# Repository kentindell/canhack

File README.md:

## Welcome to the Yes We CAN repository

This repository contains tools and resources for the <b>Yes We CAN</b> project of [Canis Labs](https://canislabs.com). There are several related projects here:

- Support for the [Canis Labs](https://canislabs.com) [CANPico](https://canislabs.com/canpico) (an add-on CAN hardware board for the Raspberry Pi Pico)
- CANHack toolkit (a proof-of-concept low-level CAN protocol hacking library)
- Sigrok CAN protocol decoder (allowing PulseView to decode CAN frames and indicate exceptional low-level protocol events)
- A Python tool for creating CAN frame bit sequences

Canis Labs CTO Dr. Ken Tindell writes about CAN on his blog at: https://kentindell.github.io

## CAN FD extension

This adds experimental **CAN FD** support to the CANHack toolkit (bit-banged, fixed
500 kbit/s arbitration / 2 Mbit/s data), from the bachelor thesis of Fynn Denecke.

- Build it from the repository root with **`./build.sh`** — see **[BUILDING.md](BUILDING.md)**
  for prerequisites (gcc/cmake/Arm toolchain) and how to point the build at your compiler.
  MicroPython is pinned as a git submodule, so the build fetches its own dependencies.
- Current hardware-verified status, known limits and a scope/PCAN test plan:
  **[CANPico/firmware/CANFD_STATUS.md](CANPico/firmware/CANFD_STATUS.md)**.

## Canis Labs CANPico hardware support

MicroPython firmware and documentation is in the `CANPico` folder. In addition, there is support for
C included in the Canis Labs CAN SDK for C, which has drivers for the MCP25xxFD (the MicroPython firmware
uses this CAN SDK to provide a MicroPython CAN API).

The Canis Labs CAN SDK repository is:

[https://github.com/kentindell/canis-can-sdk](https://github.com/kentindell/canis-can-sdk)

and contains a "hello world" application using the CAN API, with pre-built firmware for the Pico and Pico W
with the CANPico board.

## CANHack toolkit

The CANHack toolkit is a proof-of-concept toolkit of different CAN protocol attacks, showing
the viability of low-level bit-banging attacks on the CAN protocol itself.

It is provided as generic C source code in two files:

    src/
        canhack.c
        canhack.h

It has been built into the Canis Labs MicroPython firmware for the Raspberry Pi Pico and Pico W
for the following hardware:

- Canis Labs [CANPico board](https://canislabs.com/canpico/)
- Canis Labs CANHack board (this uses the same firmware as the CANPico)
- Car Hacking Village DEF CON 30 badge
- Oliver @hartkopp 's [bit-bang-only](docs/BitBangOnlyPico.md) low-cost setup

The MicroPython firmware for the CHV DEF CON 30 badge is located in:

    pico/
        micropython/
            firmware-20220805-CHV-DEFCON30.uf2

Documentation for the MicroPython CANHack API is in:

    CANPico/
        docs/
            CANHack MicroPython SDK reference manual.pdf

The Canis Labs [CTO blog](https://kentindell.github.io) has more information
[on the CANHack toolkit](https://kentindell.github.io/categories#CANHack), including details on how 
to make a CANHack board using breadboard. There is also 
a [CANHack toolkit demo video](https://youtu.be/dATyoWOlEJU) that goes into detail on how to
use the toolkit from Python, the CAN protocol hacks it
includes, and demonstrates it attacking CAN frames in real hardware (NB: the video uses the STM32-based PyBoard,
but the API is the same).

## Sigrok CAN protocol decoder

A [Sigrok](https://sigrok.org) protocol decoder for CAN 2.0:

    src/
        can2/
            __init__.py
            pd.py

There is a [PulseView and can2 demo video](https://youtu.be/RvExJSDvhKo) showing how to use PulseView
as a logic analyzer and seeing CAN frames at a low-level.

The [CIA CAN newsletter](https://https://can-newsletter.org) has published an [article](https://can-newsletter.org/tools/tools-miscellaneous/210607_can-decoder-warns-for-malicious-attacks_cnlm_ken-tindell) describing the protocol decoder and showing how it can spot some CAN protocol attacks.

## Python CAN tool

Python tool for creating and parsing a CAN bitstreams (including creating Janus attack frames):

    src/
        canframe.py

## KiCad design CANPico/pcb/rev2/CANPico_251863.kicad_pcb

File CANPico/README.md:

## CANPico support

This folder contains support files for the Canis Labs CANPico. There are two revisions of the CANPico
but the firmware operates on either version. There is also support for the Raspberry Pi Pico
and the Raspberry Pi Pico W (a Pico with wireless support). The CANPico firmware for MicroPython
includes the CANHack Toolkit as well as a CAN API.

### Hardware

There are two revisions of the hardware:

- Rev 1 uses the MCP2518FD (or the MCP2517FD) chip with an MCP2562FD CAN transceiver chip
- Rev 2 uses the MCP251863 combined CAN controller/transceiver chip

The MCP251863 is functionally an MCP2518FD CAN controller, and the Rev 2 board behaves as the
Rev 1 board and uses the same firmware.

The pinouts of both revisions are the same (although rev2 comes with solder bridges that
can be cut to free up three GPIO pins to make it easier to add other Pico boards).

Coupled to the CANPico board is a Raspberry Pi Pico or a Raspberry Pi Pico W. There is
different firmware for each: the Pico W firmware includes support for its on-board WiFi
and the new location of its on-board user LED.

The folder `pcb` contains the board design files (the CANPico was designed with Kicad).

### C SDK

The CANPico is supported by the Canis Labs C SDK with the MCP25xxFD driver. This SDK
is in the following GitHub repository and can be used by anyone with MCP25xxFD
CAN controller hardware:

[https://github.com/kentindell/canis-can-sdk](https://github.com/kentindell/canis-can-sdk)

The CAN drivers have recently been updated to implement workarounds to silicon errata in
the MCP25xxFD.

There is a "hello world" example in the repository that will build for the Pico and the
Pico W with a CANPico board.

### MicroPython SDK

The CANPico is supported with custom MicroPython firmware that provides an API for
CAN. The latest firmware is the 20230309 release and is found in the following files:

- `firmware/firmware-20230309-beta.uf2`
- `firmware/firmware-20230309-picow-beta.uf2`

This firmware is marked 'beta' because it is forked from an intermediate release of the
MicroPython firmware: the last official release of MicroPython pre-dates the Pico W
and so more recent codebase has been used. There are changes coming in MicroPython
that will be rolled into the CANPico firmware before the 'beta' status will be lifted
(most notably new official support for multiple virtual USB serial ports).

The source code for this firmware will be released at the next official MicroPython
release: merging the files for the new classes into the upstream firmware is
delicate surgery and hitting a moving target makes that extra specially difficult.

Older CANPico firmware can be found in the subfolder `firmware/OLD`. Note that older
firmware doesn't explicitly support the Pico W and although it will run on the Pico W,
none of the wireless functionality is supported.

Changes introduced by the 20230309 firmware:

- Now using the latest Canis Labs C SDK drivers for the MCP25xxFD
- Fixes to the API (e.g. the recv() calls now return an empty tuple rather than an empty list)
- Default `tx_open_drain` parameter in the `CAN()` constructor is now `True`
- New error message if the CAN controller will not set the TX open drain mode
- `get_diagnostics()` now has 6 counters, including a count of the times Bus Off happened
- Can now explicitly pass `None` to various calls to select the default

### Programming the MicroPython firmware

The firmware is programmed into a Pico or Pico W in the normal way. If programming fails
then because the bootloader is in ROM and can't be affected, it's likely the `.uf2` file has
become corrupted.

### Documentation

The documentation is available in the `docs` folder, and previous releases are in `docs/OLD`.
There is currently documentation for:

- CANPico hardware (which includes schematics for both revisions of the CANPico)
- CANPico MicroPython SDK reference manual
- CANHack MicroPython reference manual

A cheatsheet for the MicroPython API is also included.

The CAN SDK for C reference manual for the CANPico is located in the Canis Labs CAN SDK
repository given above, and examples code for the CANPico with Pico and Pico W are also 
there.

### CryptoCAN encryption of CAN frames

A MicroPython API for the Canis Labs emulated SHE HSM and CryptoCAN scheme is included
in a special release of the firmware that can be downloaded directly from the
[CryptoCAN section](https://canislabs.com/cryptocan) of the Canis Labs web site. There is
also documentation, a quick start guide, and videos.

An [article on encryption on CAN bus](https://can-newsletter.org/magazine/51-December%202022/) 
with CryptoCAN has been published in the [CAN In Automation newsletter](https://can-newsletter.org).
CryptoCAN was also presented at
the [2022 ASRG Secure our Streets conference](https://sos.asrg.io/schedule-and-presentations/).

### Other hardware

A CANHack board can be made with just breadboard and a Pico (or Pico W) to explore the
concept of CAN protocol hacking. The CANPico firmware here support such a board (but
obviously the `CAN` class will not talk to a CAN controller). There is
a [blog post on how to make a CANHack board](https://kentindell.github.io/2021/02/06/canhack-pico/)
at [Ken Tindell's blog site](https://kentindell.github.io).

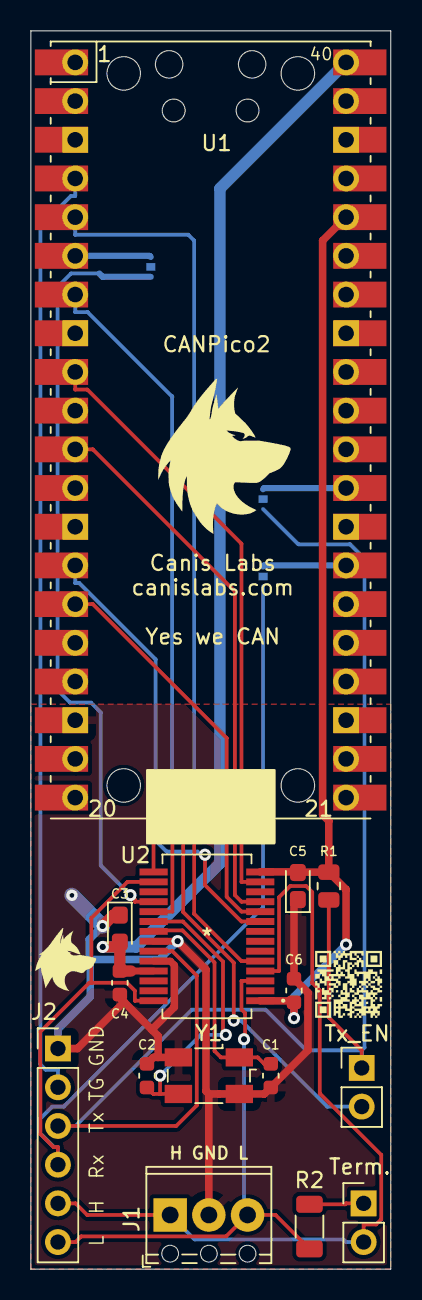
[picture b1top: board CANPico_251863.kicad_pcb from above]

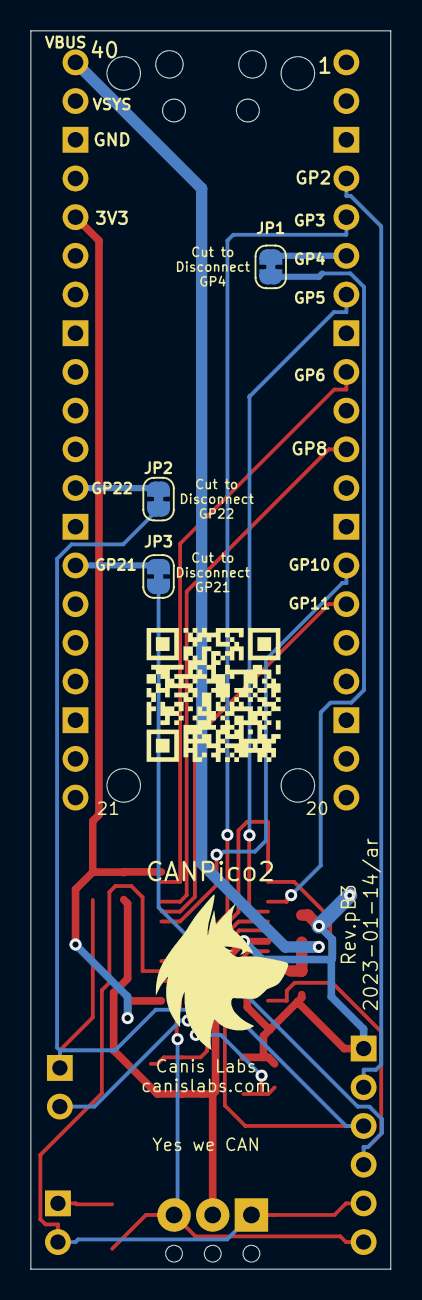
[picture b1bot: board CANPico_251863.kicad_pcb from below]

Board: 2 copper layers, 23.6 x 81.3 mm, 22 parts (3 on the bottom side), 22 nets.

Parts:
C1, C2: 22pF; C_0603_1608Metric
C3, C5: 4.7uF; CP_EIA-2012-15_AVX-P
C4, C6: 100nf; C_0603_1608Metric
H1, H2, H3, H4: MountingHole; MountingHole_2.2mm_M2_ISO14580
J1: CAN Screw Terminal; TerminalBlock_Phoenix_MPT-0,5-3-2.54_1x03_P2.54mm_Horizontal
J2: Test Connector; PinHeader_1x06_P2.54mm_Vertical
JP1, JP2, JP3: SolderJumper_2_Bridged; SolderJumper-2_P1.3mm_Bridged_RoundedPad1.0x1.5mm
JP4: Tx_EN; PinHeader_1x02_P2.54mm_Vertical
JP5: Term.; PinHeader_1x02_P2.54mm_Vertical
R1: 6k8; R_0805_2012Metric
R2: 120R; R_1206_3216Metric
U1: Pico; RPi_Pico_SMD_TH
U2: MCP251863T-E/SSVAO; MCP251863T-E&slash_SSVAO
Y1: 40MHz Crystal; Crystal_SMD_Abracon_ABM3B-4Pin_5.0x3.2mm

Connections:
+3V3: C5.2, C6.1, R1.1, U1.36 (3V3), U2.1 (VIO), U2.14 (VDD)
+5V: C3.2, C4.1, U1.40 (VBUS), U2.25 (VCC)
/CSn: U1.9 (GPIO6), U2.13 (NCS)
/H: J1.1, J2.5, JP5.2, U2.4 (CANH)
/IRQ: U1.7 (GPIO5), U2.19 (NINT)
/L: J1.3, J2.6, R2.2, U2.3 (CANL)
/Rx: J2.4, JP3.2 (B), U2.16 (RXCAN), U2.28 (RXD)
/SOF: JP1.2 (B), U2.18 (CLKO/SOF)
/SOF*: JP1.1 (A), U1.6 (GPIO4)
/SPI1_Rx: U1.11 (GPIO8), U2.11 (SDO)
/SPI1_SCK: U1.14 (GPIO10), U2.9 (SCK)
/SPI1_Tx: U1.15 (GPIO11), U2.10 (SDI)
/STBY: U1.5 (GPIO3), U2.5 (STBY)
/TRIG: J2.2, U1.4 (GPIO2)
/Tx: J2.3, JP2.2 (B), JP4.1, R1.2, U2.23 (TXD)
GND: C1.2, C2.2, C3.1, C4.2, C5.1, C6.2, J1.2, J2.1, U1.18 (GND), U2.22 (VSS), U2.24 (GND), Y1.2, Y1.4
unnamed: C1.1, U2.21 (OSC1), Y1.1
unnamed: C2.1, U2.20 (OSC2), Y1.3
unnamed: JP2.1 (A), U1.29 (GPIO22)
unnamed: JP3.1 (A), U1.27 (GPIO21)
unnamed: JP4.2, U2.15 (TXCAN)
unnamed: JP5.1, R2.1

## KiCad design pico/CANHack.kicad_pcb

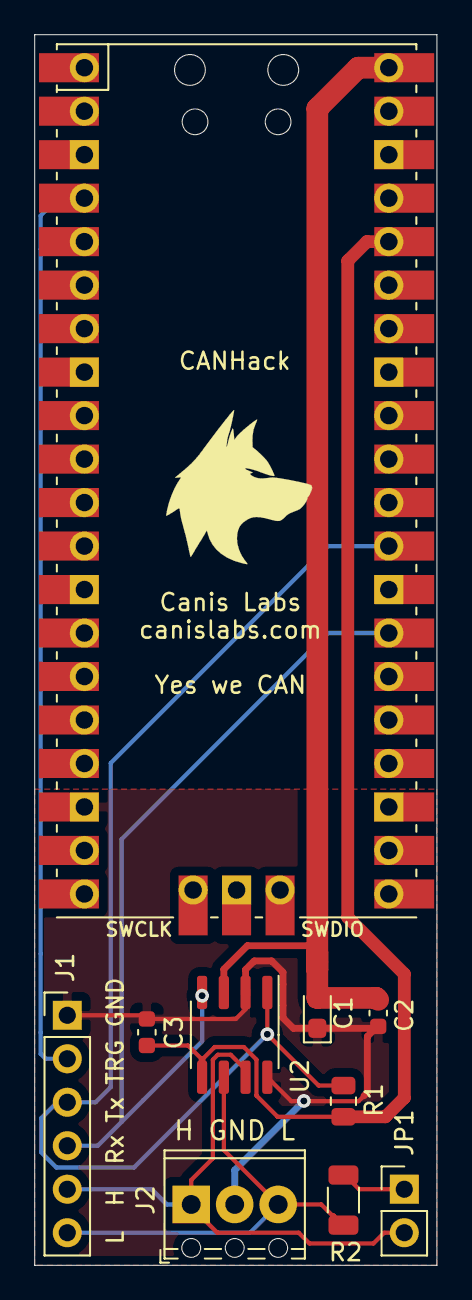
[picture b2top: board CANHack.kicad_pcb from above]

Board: 2 copper layers, 23.5 x 71.9 mm, 11 parts (1 on the bottom side), 9 nets.

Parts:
C1: 4.7uF; CP_EIA-2012-15_AVX-P
C2, C3: 100nF; C_0603_1608Metric
G2: LOGO; Canis logo 10mm
J1: Conn_01x06_Male; PinHeader_1x06_P2.54mm_Vertical
J2: Screw_Terminal_01x03; TerminalBlock_Phoenix_MPT-0,5-3-2.54_1x03_P2.54mm_Horizontal
JP1: Jumper; PinHeader_1x02_P2.54mm_Vertical
R1: 6k8; R_0805_2012Metric
R2: 120; R_1206_3216Metric
U1: Pico; RPi_Pico_SMD_TH
U2: MCP2562FD-E-SN; SOIC-8_3.9x4.9mm_P1.27mm

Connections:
+3V3: C3.2, R1.1, U1.36, U2.5
+5V: C1.2, C2.2, U1.40, U2.3
/CAN_H: J1.5, J2.1, JP1.2, U2.7
/CAN_L: J1.6, J2.3, R2.2, U2.6
/CAN_Rx: J1.4, U1.27, U2.4
/CAN_Tx: J1.3, R1.2, U1.29, U2.1
/TRIG: J1.2, U1.4
GND: C1.1, C2.1, C3.1, J1.1, J2.2, U1.18, U2.2, U2.8
unnamed: JP1.1, R2.1

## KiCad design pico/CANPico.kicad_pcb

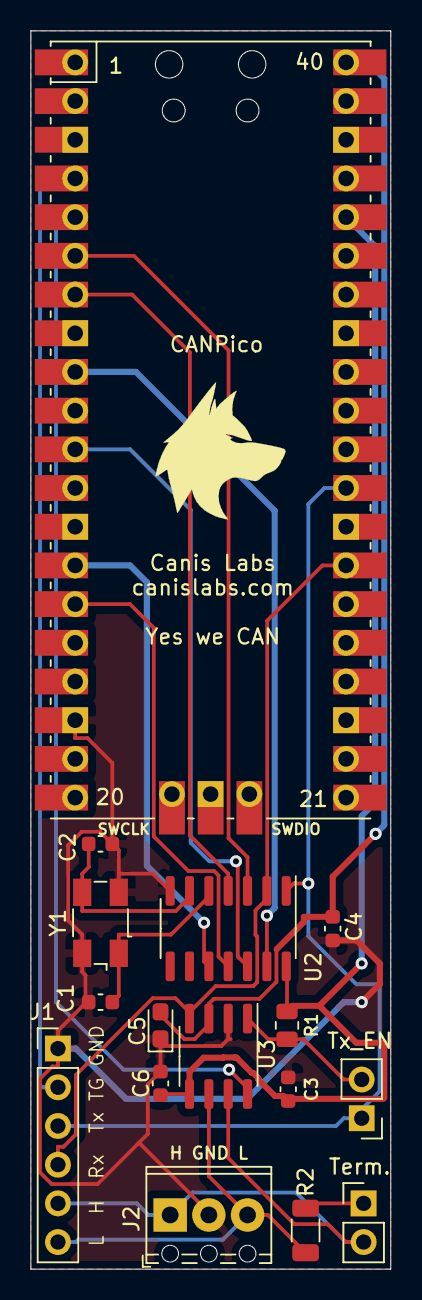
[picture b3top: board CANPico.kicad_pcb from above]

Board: 2 copper layers, 23.6 x 81.3 mm, 17 parts (1 on the bottom side), 19 nets.

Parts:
C1, C2: 22pF; C_0603_1608Metric
C3, C4, C6: 100nf; C_0603_1608Metric
C5: 4.7uF; CP_EIA-2012-15_AVX-P
G2: LOGO; Canis logo 10mm
J1: Test Connector; PinHeader_1x06_P2.54mm_Vertical
J2: CAN Connector; TerminalBlock_Phoenix_MPT-0,5-3-2.54_1x03_P2.54mm_Horizontal
JP1: Term.; PinHeader_1x02_P2.54mm_Vertical
JP2: Tx_EN; PinHeader_1x02_P2.54mm_Vertical
R1: 6k8; R_0805_2012Metric
R2: 120R; R_1206_3216Metric
U1: Pico; RPi_Pico_SMD_TH
U2: MCP2518FD-xSL; SOIC-14_3.9x8.7mm_P1.27mm
U3: MCP2562FD-x-SN; SOIC-8_3.9x4.9mm_P1.27mm
Y1: 40MHz Crystal; Crystal_SMD_Abracon_ABM3B-4Pin_5.0x3.2mm

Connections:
+3V3: C3.2, C6.1, R1.1, U1.36, U2.14, U3.5
+5V: C4.2, C5.2, U1.40, U3.3
/CSn: U1.9, U2.13
/H: J1.5, J2.1, JP1.2, U3.7
/IRQ: U1.7, U2.4
/L: J1.6, J2.3, R2.2, U3.6
/Rx: J1.4, U1.27, U2.2, U3.4
/SOF: U1.6, U2.3
/SPI1_Rx: U1.11, U2.12
/SPI1_SCK: U1.14, U2.10
/SPI1_Tx: U1.15, U2.11
/STBY: U1.5, U3.8
/TRIG: J1.2, U1.4
/Tx: J1.3, JP2.1, U1.29, U2.1
GND: C1.2, C2.2, C3.1, C4.1, C5.1, C6.2, J1.1, J2.2, U1.18, U2.7, U3.2, Y1.2, Y1.4
unnamed: C1.1, U2.5, Y1.1
unnamed: C2.1, U2.6, Y1.3
unnamed: JP1.1, R2.1
unnamed: JP2.2, R1.2, U3.1

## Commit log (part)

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2020-01-03 First version of the CAN frame generator
2020-01-03 Set theme jekyll-theme-minimal
2020-01-22 First release of CANHack toolkit source
2020-01-22 Fixed broken URL
2020-08-16 Coming soon..
2020-08-16 Raspberry Pi with a CAN board and internet access
2020-10-25 Error and display changes and new decode function
2020-12-19 First commit of can2 decoder
2021-01-02 Added binary output in pcapng format
2021-01-02 Updated README with link to blog post about can2
2021-01-09 Updated initialization to find sample rate
2021-02-06 Bug fix: export frame details only if error free
2021-02-06 Moved CANHack to the Raspberry Pi Pico
2021-02-06 MicroPython CANHack toolkit for Pi Pico
2021-02-06 Updated README for the new Pi Pico CANHack release
2021-02-06 New Pi Pico CANHack release
2021-02-15 Updated README with new links
2021-03-10 Squashed commit of the following:
    commit a5e92ffee85fd63b27458b9720a32a0716ad7101
    Author: Ken Tindell <ken.tindell@jkenergy.com>
    Date: Wed Mar 10 17:08:36 2021 +0000
    Documentation for CAN and CANHack
2021-03-10 Added .nojekyll to allow browsing HTML documentation
2021-03-10 Disable Jekyll
2021-03-10 Moved Sphinx HTML
2021-03-10 Edited README with link to documentation
2021-03-15 Added ASCII display option
2021-05-17 New firmware and documentation
2021-05-17 Corrupted firmware file
2021-05-17 Added MD5 hash of firmware file
2021-05-18 Renamed documents to omit versioning
2021-05-18 Filename changes
2021-07-09 can2: add some shorter format options for IDs
2021-07-09 can2: add some shorter format options for data bytes (when not showing ASCII)
2021-07-09 can2: add CAN string payload to 'data'/'Payload', use same hex or hex+ascii option
2021-07-09 swap the bytewise 'can-payload' into the fields row and the string 'data' into the payload row
2021-07-09 can2: avoid python byte escaping display when hex+ascii is selected
2021-07-13 Updated MicroPython API reference manual and CANHack schematics
2021-07-13 Added TODO to support smart CAN triggers with CANPico
2021-07-13 Updated to MicroPython v1.16, improved robustness to SPI noise
2021-07-13 Extra support for interactive examples
2021-07-13 Added simple example: finding Janus frames
2021-07-14 Updated falling edge to use CAN hard sync
2021-07-16 Added a periodic frame sender
2022-04-06 Updated README.txt
    Location of v1.15.patch (which includes the canis folder and CAN drivers)
2022-04-26 Updated to v1.18 of MicroPython
2022-04-28 Added missing file
2022-05-04 Update README.txt
    Added note for building firmware on a Mac
2022-05-11 New firmware with mincan module baked in
2022-05-11 Release of CANPicoCtrl v1.0
2022-08-05 New CHV DEF CON 30 badge firmware
2022-08-05 New version of CANPico MicroPython reference manual
2022-08-05 MicroPython firmware using new CAN SDK
2023-03-12 New CANPico folder
2023-03-12 README edits
2023-03-12 Added PDF documents for CANPico
2023-03-12 Archived old CANPico documents
2023-03-12 CANPico 20230309 firmware
2023-03-12 Archived previous firmware
2023-03-12 Added pinout for CANPico
2023-03-12 Try #2 to upload a binary file
2023-03-13 Added rev2 hardware schematics and Kicad files
2023-04-12 First cut at measuring recessive pulses
2023-04-17 Added node identification import/export via JSON
2023-04-17 Working with slow Logic Analyzer
2023-04-19 Replaced .hex() with code for older Pythons
2023-04-21 Bug fixes; write to JSON now an option
2023-08-14 fix a decoder exception due to missing IDE field. Triggered by processing pathological traces from Tom Forest's Unrealistic CAN challenge CHV CTF 2023
2023-09-12 can2: format strings are not supported in python 3.4
2023-09-12 can2: module 'typing' is not avaiable in python 3.4
    ... also the import is strictly needed for the comment-style type
    hinting
2023-09-12 remove the duplicate canhack.{c,h} files
2024-03-28 initial version
2024-04-01 Moved to v1.22.2 upstream MicroPython
2024-04-01 Datestamp/tag firmware

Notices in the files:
CANPico/pcb/rev2/CANPico_251863.kicad_pcb:
©2023 Canis/ar
pico/CANPico.kicad_pcb:
©2021 Canis/ar
parts and their libraries:
Copyright 2021 Accelerated Designs. All rights reserved.
